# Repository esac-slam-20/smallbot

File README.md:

# Project-SmallBot

小车制作计划

## 需求

- 带相机，能够图传（回来）
- 带激光雷达，能导航
- IMU？

## 需求分析

1. 算力要足够，所以使用树莓派4B
2. 底盘打算使用3个电机以120度的角度安装全向轮。
3. 树莓派4B的IO口不足以驱动3个电机（6个IO）+3个编码器（3/6个IO，取决于编码器类型），故需要额外单片机
   1. 单片机的电平一般是3.3V的，而驱动控制电平是5V的，所以要做电平转换。
   2. 需要3路PWM和3路正交译码器，这样能够保证最快速度；再加上3/6个GPIO做方向切换。
   3. TB6612好像比L298N好一点，电流也算够，一个电机只要 1 PWM + 2 GPIO 即可。
4. 由于使用了12V的电机，电池组需要使用大于12V的电池，即3*3.7=11.1v（max 13.2v）
   1. 因此，树莓派供电要额外做降压
   2. 也要做充电接口，并且有要充电模块（或者充电器）
   3. 如果放弃外置充电器而使用Type-C，则需要 PD 诱骗器诱骗出15V，共给 SY6912 再接电池供电
   4. 使用动力电池包 or 买动力18650 + 保护板？
5. 激光雷达是5V的，直接从树莓派供电即可；并且走的是串口，直接接就行。
6. 相机图传走Wifi
7. （可选）IMU是I2C接口，并且是3.3V供电，可以直接接树莓派。BMX055看上去够便宜？
8. 单片机的选型
   1. 需要3路PWM和3路正交译码器，这些功能一般由Timer提供
   2. 不要STM32，太贵了
   3. 最终选定 GD32VF103CBT6（开发板），带4路PWM和4路正交译码器，可以最大支持四个电机。

## 硬件版本

| 版本号 | V1 | V2 | V3 |
| ----------| -------- | -------- | -------- |
| 日期 | 2021/07 | 2021/09 | 2023/04 |
| 主控 | GD32VF103CBT6(核心板) | GD32VF103CBT6 | CH32V103CBT6 |
| 电机驱动 | TB6612(模块) | TB6612 | DRV8870（AT4950） |
| USB充电 | 是(PD 15V) | 是(宽电压) | 否 |
| IMU | 预留接口 | 预留接口 | 有 |
| 激光雷达 | 无 | 预留接口 | 预留接口 |
| 电机数量 | 4 | 4 | 3+1(舵机) |
| 电池接口 | XT60 | XT60 | XT30 |

## 材料列表

- 主控：树莓派4b, 4G
- 电池：5000mah
- 摄像头：单目/30fps/720p
- 激光雷达：有数据就行
- 电机：普通电机即可，12V
- 轮子：3个全向轮
- 底盘亚克力
- 驱动：TB6612驱动 * 2 = 4路
- 单片机：GD32VF103CBT6（Longan Nano 开发板）

## 价格表

| 物品       | 数量 | 单价 |
| ---------- | ---- | ---- |
| 树莓派     | 1    | 350  |
| 电池       | 1    | 54   |
| 摄像头     | 1    | 70   |
| 激光雷达   | 1    | 115  |
| 电机       | 3    | 50   |
| 轮子       | 3    | 25   |
| 亚克力底盘 | 1    | 50   |
| 电机驱动   | 2    | 7    |
| 单片机     | 1    | 20   |

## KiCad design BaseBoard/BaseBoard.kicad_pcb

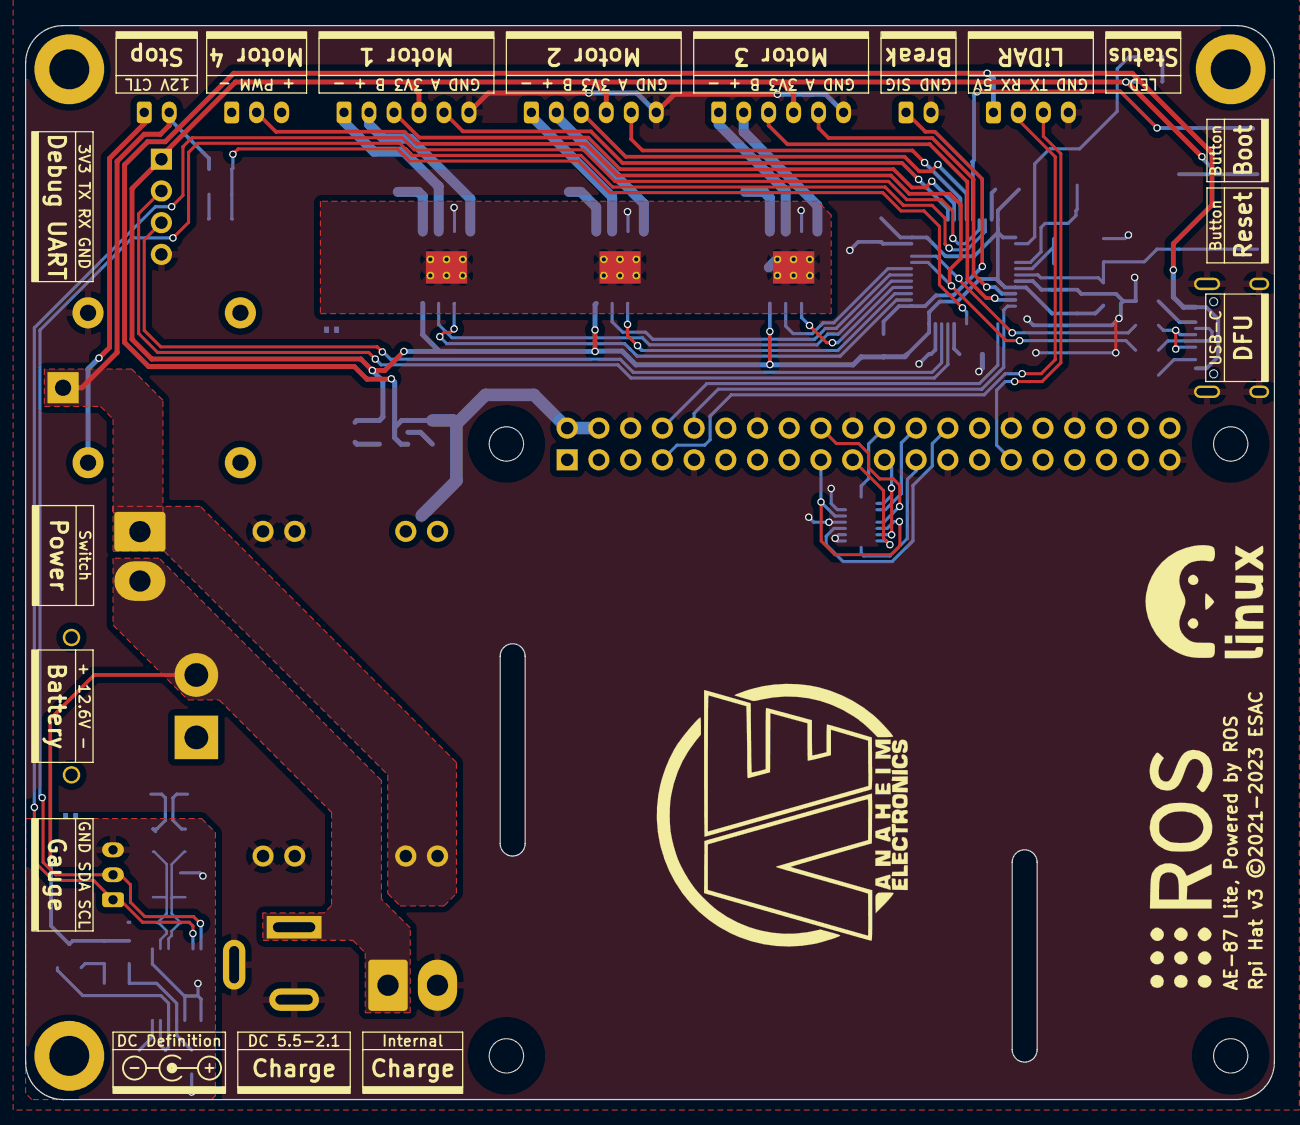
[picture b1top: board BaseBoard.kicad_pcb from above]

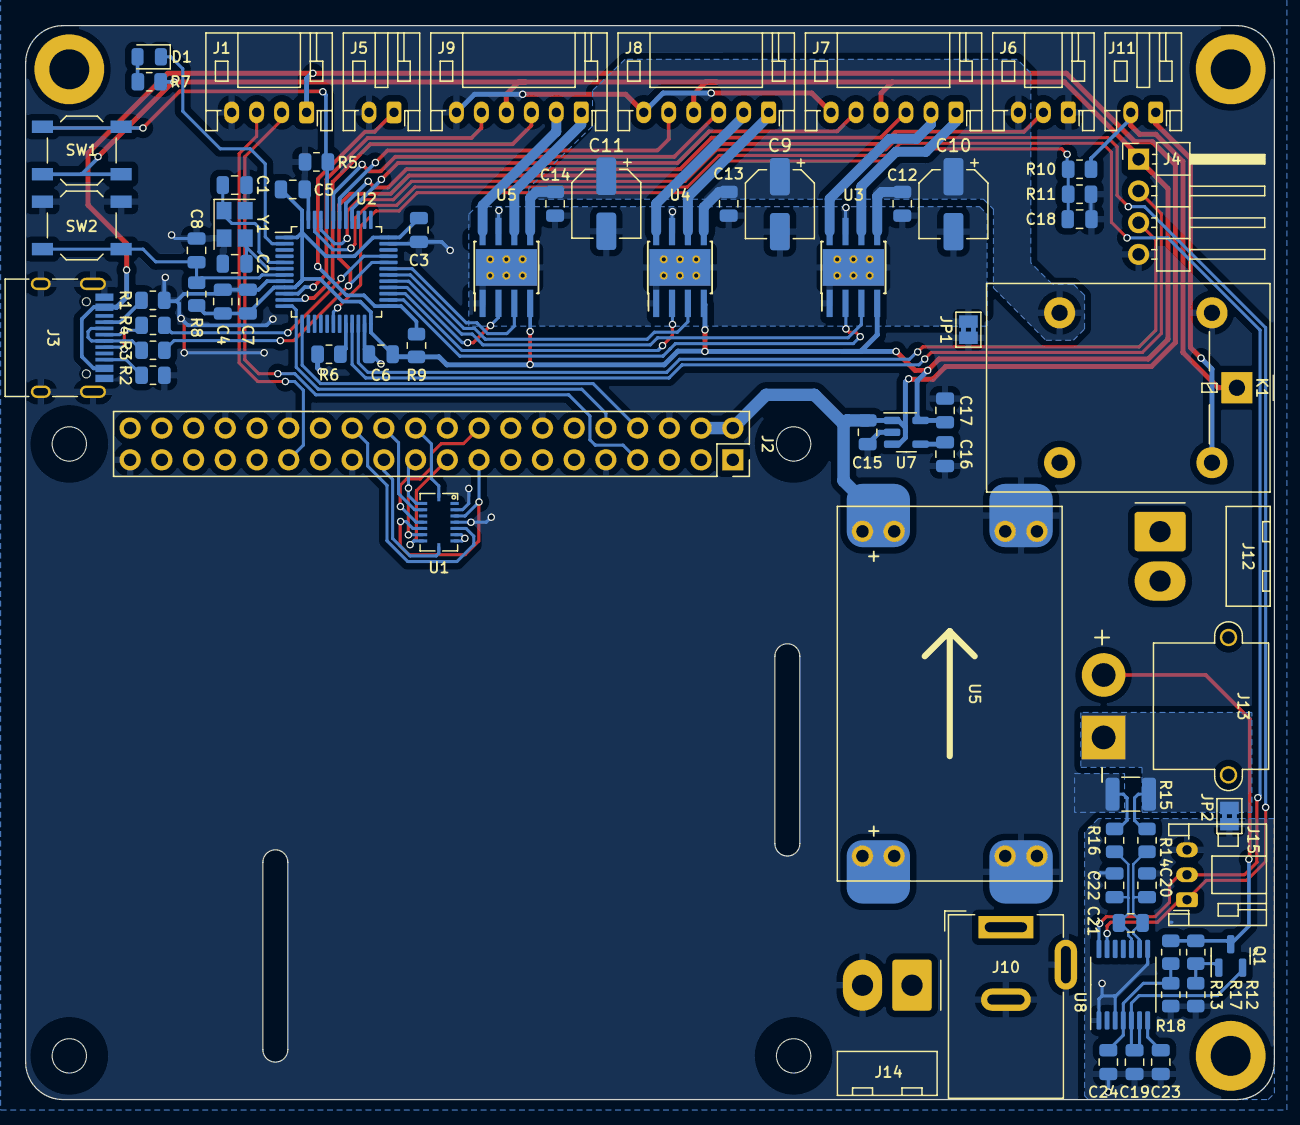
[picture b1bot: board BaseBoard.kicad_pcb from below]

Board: 2 copper layers, 100.0 x 86.0 mm, 76 parts (73 on the bottom side), 66 nets.

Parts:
C1, C2: 12pF; C_0805_2012Metric
C3, C4, C5, C6, C7, C8, C12, C13, C14, C16, C18, C19, C20, C21, C22, C23: 100nF; C_0805_2012Metric
C9, C10, C11: 47uF; CP_Elec_5x5.4
C15, C17: 1uF; C_0805_2012Metric
C24: 3.3nF; C_0805_2012Metric
D1: LED_White; LED_0805_2012Metric
J1: PH2.0_1x04; JST_PH_S4B-PH-K_1x04_P2.00mm_Horizontal
J2: Raspberry_Pi_2_3; PinSocket_2x20_P2.54mm_Vertical
J3: USB_C_Receptacle_USB2.0; USB_C_Receptacle_HRO_TYPE-C-31-M-12
J4: PinHeader_2.54_1x04; PinHeader_1x04_P2.54mm_Horizontal
J5, J11: PH2.0_1x02; JST_PH_S2B-PH-K_1x02_P2.00mm_Horizontal
J6, J15: PH2.0_1x03; JST_PH_S3B-PH-K_1x03_P2.00mm_Horizontal
J7, J8, J9: PH2.0_1x06; JST_PH_S6B-PH-K_1x06_P2.00mm_Horizontal
J10: DC5.5/2.1; BarrelJack_Wuerth_6941xx301002
J12, J14: HT396R_1x02; Molex_KK-396_A-41792-0002_1x02_P3.96mm_Horizontal
J13: XT30PW; AMASS_XT30PW-M_1x02_P2.50mm_Horizontal
JP1, JP2: NC; SolderJumper-2_P1.3mm_Bridged2Bar_Pad1.0x1.5mm
K1: SRD-12V; Relay_SPDT_Omron-G5LE-1
LOGO1: Logo_ROS; ROS_LOGO_20x6
LOGO2: Logo_Linux; Linux_12x12
LOGO3: Logo_Anaheim_Electronic; Anaheim_Electronic_20
Q1: 2N7002; SOT-23
R1, R2: 5.1k; R_0805_2012Metric
R3, R4: 22R; R_0805_2012Metric
R5, R6, R7, R8, R9: 10k; R_0805_2012Metric
R10: 360k; R_0805_2012Metric
R11, R13: 100k; R_0805_2012Metric
R12, R17: 220k; R_0805_2012Metric
R14, R16: 100R; R_0805_2012Metric
R15: 10mR; R_1210_3225Metric
R18: 16.5k; R_0805_2012Metric
SW1, SW2: TL3342; SW_SPST_TL3342
U1: BMI088; Bochs_LGA16_2x7+2x1
U2: GD32VF103C8Tx; LQFP-48_7x7mm_P0.5mm
U3, U4, U5#2: DRV8870DDA; Texas_HTSOP-8-1EP_3.9x4.9mm_P1.27mm_EP2.95x4.9mm_Mask2.4x3.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
U5: MINI560; Converter_DCDC_Mini_560
U7: SGM2028-3.3YN5G; SOT-23-5
U8: BQ34Z100; TSSOP-14_4.4x5mm_P0.65mm
Y1: 8MHz; Crystal_SMD_3225-4Pin_3.2x2.5mm

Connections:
+3.3VA: J2.1 (3V3), J2.17 (3V3), U1.3 (VDD), U1.11 (VDDIO)
+3V3: C3.1, C4.1, C5.1, C6.1, C7.2, C17.1, J4.1, J7.4, J8.4, J9.4, R7.1, R8.2, R9.1, SW1.2, U2.1 (VBAT), U2.9 (VDDA), U2.24 (VDD), U2.36 (VDD), U2.48 (VDD), U3.4 (VREF), U4.4 (VREF), U5#2.4 (VREF), U7.5 (OUT)
+5V: C15.1, J1.1, J2.2 (5V), J2.4 (5V), J3.A4 (VBUS), J3.A9 (VBUS), J3.B4 (VBUS), J3.B9 (VBUS), U5.3 (OUT), U7.1 (IN), U7.3 (EN)
+12V: J11.2, J12.1, K1.1, R10.1, U5.1 (IN)
+12VA: C9.1, C10.1, C11.1, C12.1, C13.1, C14.1, J6.3, K1.3, U3.5 (VM), U4.5 (VM), U5#2.5 (VM)
+BATT: J10.1, J12.2, J13.2, J14.1, Q1.3 (D), R12.1, R17.1
-BATT: J13.1, JP2.1 (A), R14.2, R15.1
/ADC: C18.1, R10.2, R11.1, U2.18 (PB0)
/BOOT0: R5.1, SW1.1, U2.44 (BOOT0)
/BOOT1: R6.1, U2.20 (PB2)
/BREAK: J5.1, R9.2, U2.25 (PB12)
/CTL_RX: J2.8 (GPIO14/TXD), U2.13 (PA3)
/CTL_TX: J2.10 (GPIO15/RXD), U2.12 (PA2)
/DEBUG_RX: J4.3, U2.22 (PB11)
/DEBUG_TX: J4.2, U2.21 (PB10)
/ENC1_A: J7.5, U2.40 (PB4)
/ENC1_B: J7.3, U2.41 (PB5)
/ENC2_A: J8.5, U2.42 (PB6)
/ENC2_B: J8.3, U2.43 (PB7)
/ENC3_A: J9.5, U2.10 (PA0)
/ENC3_B: J9.3, U2.11 (PA1)
/I2C_SCL: J15.1, U2.45 (PB8), U8.13 (P4/SCL)
/I2C_SDA: J15.2, U2.46 (PB9), U8.14 (P3/SDA)
/IMU_INT1: J2.22 (GPIO25), U1.16 (INT1)
/IMU_INT2: J2.18 (GPIO24), U1.12 (INT3)
/LIDAR_RX: J1.2, J2.7 (GCLK0/GPIO4)
/LIDAR_TX: J1.3, J2.29 (GCLK1/GPIO5)
/Motor/MOT1_N: J7.1, U3.6 (OUT1)
/Motor/MOT1_P: J7.2, U3.8 (OUT2)
/Motor/MOT2_N: J8.1, U4.6 (OUT1)
/Motor/MOT2_P: J8.2, U4.8 (OUT2)
/Motor/MOT3_N: J9.1, U5#2.6 (OUT1)
/Motor/MOT3_P: J9.2, U5#2.8 (OUT2)
/OSCIN: C1.1, U2.5 (PD0), Y1.1
/OSCOUT: C2.1, U2.6 (PD1), Y1.3
/PWM1: U2.29 (PA8), U3.3 (IN1)
/PWM1_ON: U2.26 (PB13), U3.2 (IN2)
/PWM2: U2.30 (PA9), U4.3 (IN1)
/PWM2_ON: U2.27 (PB14), U4.2 (IN2)
/PWM3: U2.31 (PA10), U5#2.3 (IN1)
/PWM3_ON: U2.28 (PB15), U5#2.2 (IN2)
/PWM4: J6.2, R3.1, U2.32 (PA11)
/Power/CTRL: J11.1, K1.5
/Power/SRN: C21.2, C22.1, R16.1, U8.10 (SRN)
/Power/SRP: C20.1, C21.1, R14.1, U8.9 (SRP)
/SPI_CLK: J2.23 (SCLK0/GPIO11), U1.8 (SCL/CLK)
/SPI_CS1: J2.24 (~CE0/GPIO8), U1.14 (CSB1)
/SPI_CS2: J2.26 (~CE1/GPIO7), U1.5 (CSB2)
/SPI_MISO: J2.21 (MISO0/GPIO9), U1.10 (MISO2), U1.15 (MISO1)
/SPI_MOSI: J2.19 (MOSI0/GPIO10), U1.9 (SDA/MOSI)
/USB_DP: R4.1, U2.33 (PA12)
GND: C1.2, C2.2, C3.2, C4.2, C5.2, C6.2, C7.1, C8.2, C15.2, C16.2, C17.2, C18.2, J1.4, J2.6 (GND), J2.9 (GND), J2.14 (GND), J2.20 (GND), J2.25 (GND), J2.30 (GND), J2.34 (GND), J2.39 (GND), J3.A1 (GND), J3.A12 (GND), J3.B1 (GND), J3.B12 (GND), J3.S1 (SHIELD), J4.4, J5.2, J6.1, J7.6, J8.6, J9.6, J10.2, J10.3, J14.2, JP1.1 (A), K1.2, R1.1, R2.1, R5.2, R6.2, R11.2, R15.2, R16.2, SW2.2, U1.2 (NC), U1.4 (GNDA), U1.6 (GNDIO), U1.7 (PS), U2.8 (VSSA), U2.23 (VSS), U2.35 (VSS), U2.47 (VSS), U5.2 (GND), U7.2 (GND), Y1.2, Y1.4
GNDA: C19.2, C20.2, C22.2, C23.2, C24.2, J15.3, JP2.2 (B), R13.2, R18.2, U8.1 (P2), U8.3 (P1), U8.8 (VSS)
GNDPWR: C9.2, C10.2, C11.2, C12.2, C13.2, C14.2, JP1.2 (B), U3.1 (GND), U3.7 (ISEN), U3.9 (GND), U4.1 (GND), U4.7 (ISEN), U4.9 (GND), U5#2.1 (GND), U5#2.7 (ISEN), U5#2.9 (GND)
unnamed: D1.2 (A), R7.2
unnamed: D1.1 (K), U2.2 (PC13)
unnamed: J3.A5 (CC1), R1.2
unnamed: J3.B5 (CC2), R2.2
unnamed: J3.A6 (D+), J3.B6 (D+), R4.2
unnamed: J3.A7 (D-), J3.B7 (D-), R3.2
unnamed: Q1.1 (G), R12.2, R13.1
unnamed: C19.1, Q1.2 (S), U8.5 (CE), U8.6 (REGIN)
unnamed: C8.1, R8.1, SW2.1, U2.7 (NRST)
unnamed: C16.1, U7.4 (BP)
unnamed: C24.1, R17.2, R18.1, U8.4 (BAT)
unnamed: C23.1, U8.7 (REG25)

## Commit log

2021-07-01 更新 'README.md'
2021-07-01 添加需求分析和物料列表
2021-07-10 完成主控板的绘制，添加一些数据手册
2021-07-13 添加BOM，板子上添加IMU接口
2021-07-14 更新线路板布局
2021-07-23 更新线路板设计，添加PD芯片
2021-07-23 更新BOM
2021-07-26 添加树莓派的数据手册
2021-07-27 修正一处电阻阻值错误的问题
2021-08-02 添加使用手册
2021-08-02 更新 'Manual.md'
    添加串口的启用说明
2021-08-04 添加小车方向定义说明
2021-08-05 更新 'Manual.md'
2021-08-10 v2板临时提交
2021-08-28 v2提交
2021-08-29 添加备份封装库
2021-09-01 Modify some footprints.
2021-09-09 修正两处电阻阻值不正确的问题
2021-09-14 添加V2版本主控说明书
2022-06-29 V3 Baseboard
2023-03-12 使用功率地
2023-04-07 临时提交
2023-04-09 更新V3线路板
2023-04-09 添加v3初版设计
2023-04-19 调整孔位置
2023-04-24 修改部分封装和值
2023-06-11 Update documents
2023-06-11 docs: add CH32V103 datasheets

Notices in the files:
BaseBoard/BaseBoard.kicad_pcb:
Rpi Hat v3 ©2021-2023 ESAC
